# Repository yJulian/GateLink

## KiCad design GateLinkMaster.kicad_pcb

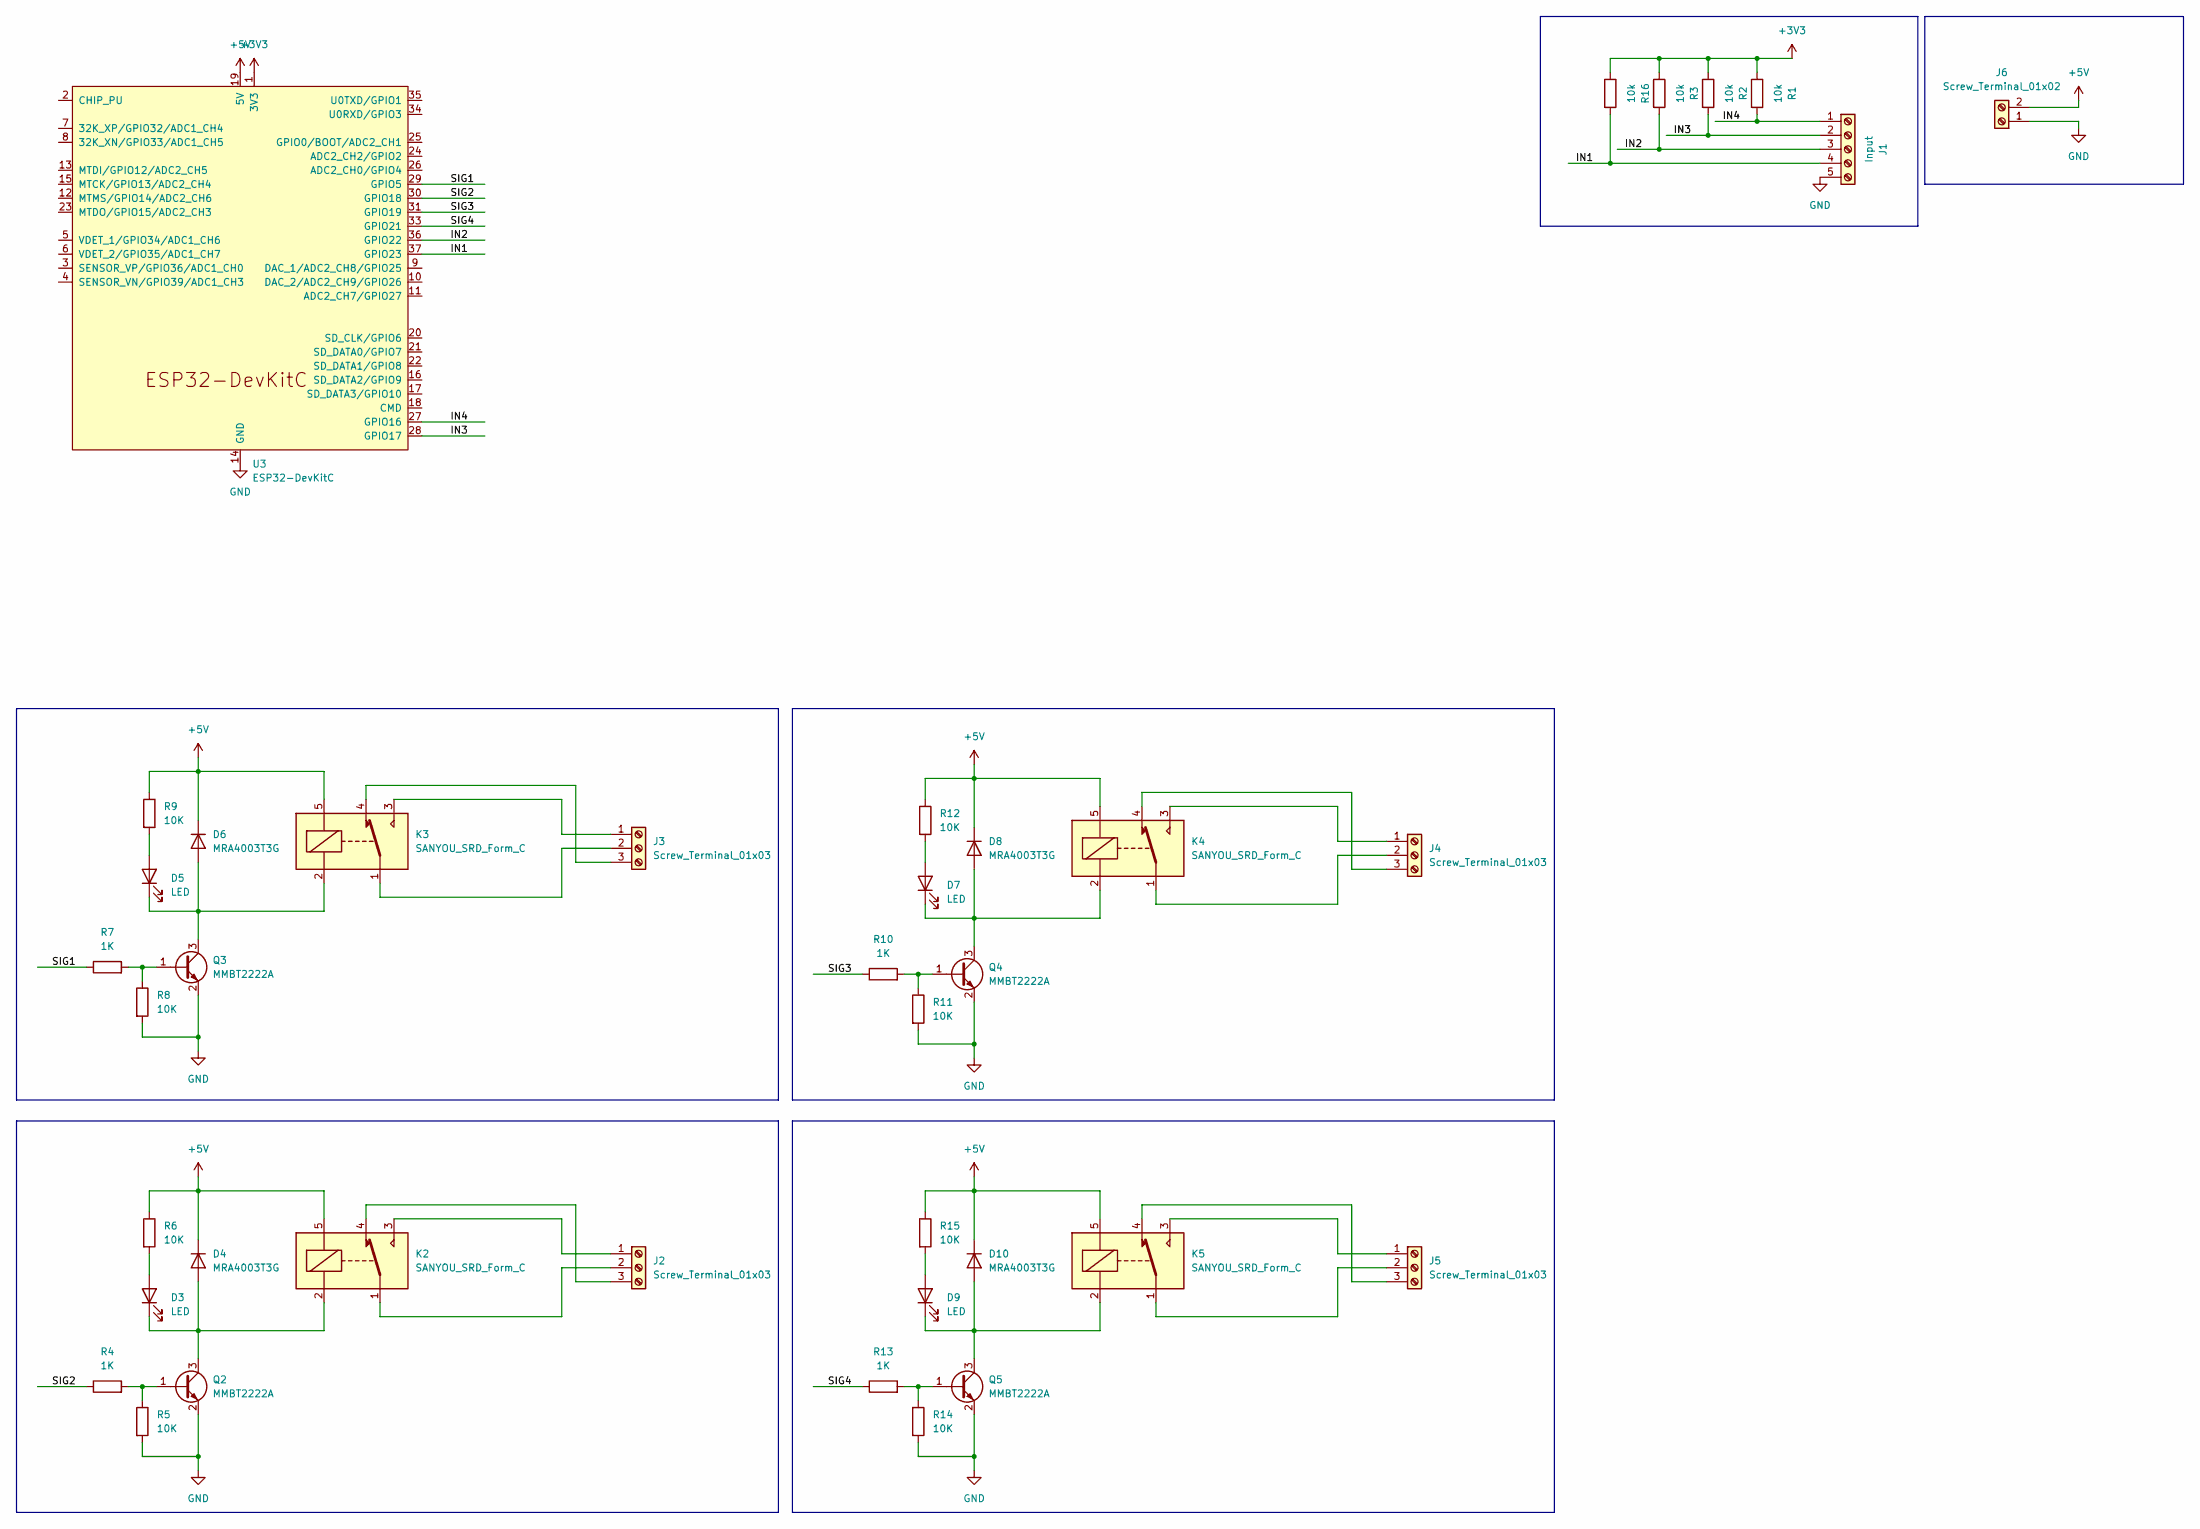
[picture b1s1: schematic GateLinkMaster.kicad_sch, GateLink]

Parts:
D3, D5, D7, D9: LED; LED_0603_1608Metric
D4, D6, D8, D10: MRA4003T3G; D_SMA
J1: Input; TerminalBlock_MaiXu_MX126-5.0-05P_1x05_P5.00mm
J2, J3, J4, J5: Screw_Terminal_01x03; TerminalBlock_MaiXu_MX126-5.0-03P_1x03_P5.00mm
J6: Screw_Terminal_01x02; TerminalBlock_MaiXu_MX126-5.0-02P_1x02_P5.00mm
K2, K3, K4, K5: SANYOU_SRD_Form_C; Relay_SPDT_SANYOU_SRD_Series_Form_C
Q2, Q3, Q4, Q5: MMBT2222A; SOT-23
R1, R2, R3, R16: 10k; R_0603_1608Metric
R4, R7, R10, R13: 1K; R_0603_1608Metric
R5, R6, R8, R9, R11, R12, R14, R15: 10K; R_0603_1608Metric
U3: ESP32-DevKitC

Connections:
+3V3: R1.1, R2.1, R3.1, R16.1, U3.1 (3V3)
+5V: D4.1 (K), D6.1 (K), D8.1 (K), D10.1 (K), J6.2, K2.5, K3.5, K4.5, K5.5, R6.1, R9.1, R12.1, R15.1, U3.19 (5V)
/IN1: J1.4, R16.2, U3.37 (GPIO23)
/IN2: J1.3, R3.2, U3.36 (GPIO22)
/IN3: J1.2, R2.2, U3.28 (GPIO17)
/IN4: J1.1, R1.2, U3.27 (GPIO16)
/SIG1: R7.1, U3.29 (GPIO5)
/SIG2: R4.1, U3.30 (GPIO18)
/SIG3: R10.1, U3.31 (GPIO19)
/SIG4: R13.1, U3.33 (GPIO21)
GND: J1.5, J6.1, Q2.2 (E), Q3.2 (E), Q4.2 (E), Q5.2 (E), R5.2, R8.2, R11.2, R14.2, U3.14 (GND), U3.32 (GND), U3.38 (GND)
unnamed: D3.2 (A), R6.2
unnamed: D3.1 (K), D4.2 (A), K2.2, Q2.3 (C)
unnamed: D5.2 (A), R9.2
unnamed: D5.1 (K), D6.2 (A), K3.2, Q3.3 (C)
unnamed: D7.2 (A), R12.2
unnamed: D7.1 (K), D8.2 (A), K4.2, Q4.3 (C)
unnamed: D9.2 (A), R15.2
unnamed: D9.1 (K), D10.2 (A), K5.2, Q5.3 (C)
unnamed: J2.1, K2.3
unnamed: J2.2, K2.1
unnamed: J2.3, K2.4
unnamed: J3.1, K3.3
unnamed: J3.2, K3.1
unnamed: J3.3, K3.4
unnamed: J4.1, K4.3
unnamed: J4.2, K4.1
unnamed: J4.3, K4.4
unnamed: J5.1, K5.3
unnamed: J5.2, K5.1
unnamed: J5.3, K5.4
unnamed: Q2.1 (B), R4.2, R5.1
unnamed: Q3.1 (B), R7.2, R8.1
unnamed: Q4.1 (B), R10.2, R11.1
unnamed: Q5.1 (B), R13.2, R14.1

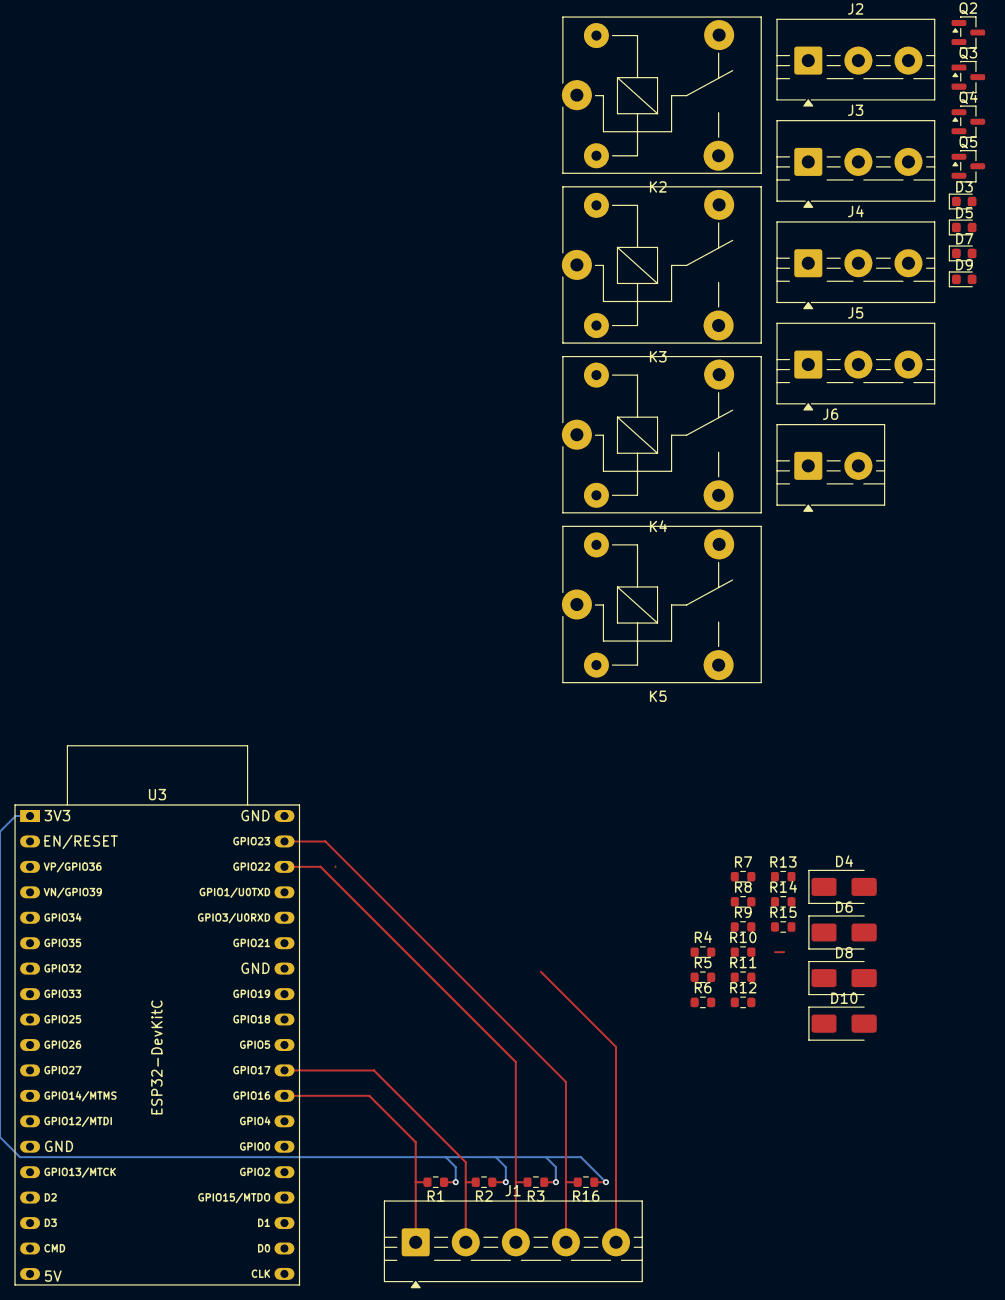
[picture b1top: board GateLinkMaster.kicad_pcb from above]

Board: 2 copper layers, 39 parts (0 on the bottom side), 35 nets.

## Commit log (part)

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2025-11-08 init
2025-11-09 CP2102
2025-11-12 jesus
